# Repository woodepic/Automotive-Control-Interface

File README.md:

# Automotive-Control-Interface
A seamless user experience is critical for a well-engineered product. This project integrates a retrofitted button into the car's existing button backlighting system. This project includes designing the button, control interface, animations, and firmware from scratch. 

I wanted to add a button to my car for aftermarket heated windshield wipers, however I wanted to integrate it seamlessly into the vehicle. My car uses a single dimming control to dim every button and every screen in the car, so I wanted this existing dimmer to also dim my new button. This led me to tap into an existing button's backlight, use a voltage divider in my pcb to allow the arduino to read the signal, and use the arduino to measure the pulse width. Using a simple mapping function and the transisor-switched 12V power on my PCB, I can now match the new button's backlight to that of the car's. 

Image of the control PCB and the button:

I also wanted the button to look as though it belonged in the car. This led me to design and order a custom button. I designed a logo to indicate heated wipers, and ordered the button as a momentary, silver button, with a matching red backlight. Whenever the button is toggled on, a pulsing animation in the button's backlight begins. Whenever the button is off, the backlight matches that of other buttons, meaning in the daytime mode the backlight is off, and in the night-time mode the backlight is on. See the link at the bottom of this readme for a video demo. 

The arduino accepts various inputs: The momentary signal from the wiper button and the PWM signal from the car's existing button. The arduino calculates, and manages various outputs: power to the wiper button's backlight, a signal to a relay (toggles on/off the high-powered heated wipers), and an auxilary brightness output used to control the brightness of an aftermarket gauge.

As the cherry on top, all of the code including pulse animations are written to be non blocking, allowing other code to execute at the same time. I also implemented safety features such as built in fuses, a default to "wiper heat off" upon boot, and the power relay defaults to off in case of arduino failure.

Demo video of the project is found here: <https://youtu.be/XevvCuZYbWQ>

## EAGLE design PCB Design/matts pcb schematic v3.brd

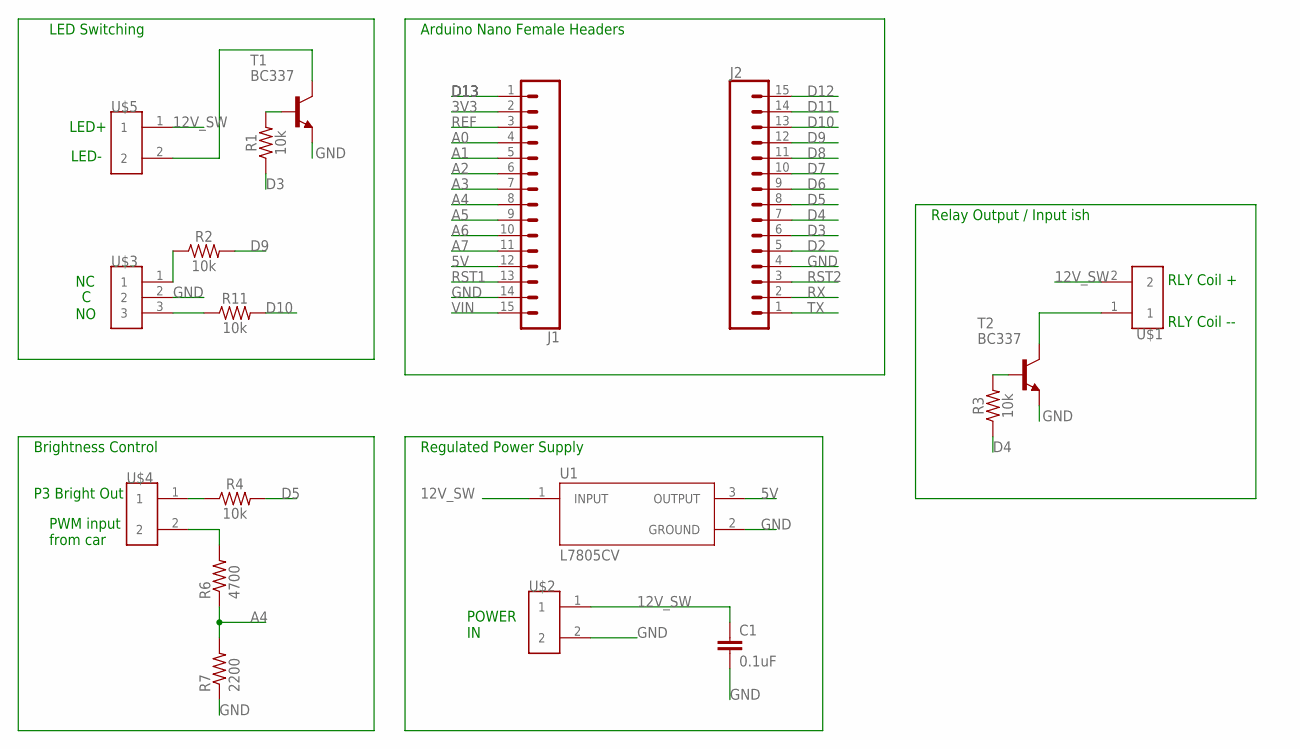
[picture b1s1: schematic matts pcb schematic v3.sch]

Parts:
C1: 0.1uF; CAP-PTH-SMALL-KIT
J1, J2: CONN_15; 1X15
R1, R2, R3, R4, R11: 10k; AXIAL-0.3
R6: 4700; 0207/10
R7: 2200; 0207/10
T1, T2: BC337; TO92
U1: L7805CV; TO255P1040X460X1968-3
U$1, U$2, U$4, U$5: 2PIN_0.2PITCH_SCREW_TERMINAL
U$3: 3PIN_0.2PITCH_SCREW_TERMINAL

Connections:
3V3: J1.2
5V: J1.12, U1.3 (OUTPUT)
12V_SW: C1.1, U1.1 (INPUT), U$1.2, U$2.1, U$5.1
A0: J1.4
A1: J1.5
A2: J1.6
A3: J1.7
A4: J1.8, R6.1, R7.2
A5: J1.9
A6: J1.10
A7: J1.11
D2: J2.5
D3: J2.6, R1.P$1 (1)
D4: J2.7, R3.P$1 (1)
D5: J2.8, R4.P$2 (2)
D6: J2.9
D7: J2.10
D8: J2.11
D9: J2.12, R2.P$2 (2)
D10: J2.13, R11.P$2 (2)
D11: J2.14
D12: J2.15
D13: J1.1
GND: C1.2, J1.14, J2.4, R7.1, T1.1 (E), T2.1 (E), U1.2 (GROUND), U$2.2, U$3.2
unnamed: R2.P$1 (1), U$3.1
unnamed: T2.3 (C), U$1.1
unnamed: R4.P$1 (1), U$4.1
unnamed: T1.3 (C), U$5.2
unnamed: R3.P$2 (2), T2.2 (B)
unnamed: R1.P$2 (2), T1.2 (B)
unnamed: R6.2, U$4.2
unnamed: R11.P$1 (1), U$3.3
REF: J1.3
RST1: J1.13
RST2: J2.3
RX: J2.2
TX: J2.1
VIN: J1.15

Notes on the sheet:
Arduino Nano Female Headers
LED+
LED-
Regulated Power Supply
LED Switching
Relay Output / Input ish
RLY Coil +
RLY Coil --
Brightness Control
P3 Bright Out
PWM input from car
POWER IN

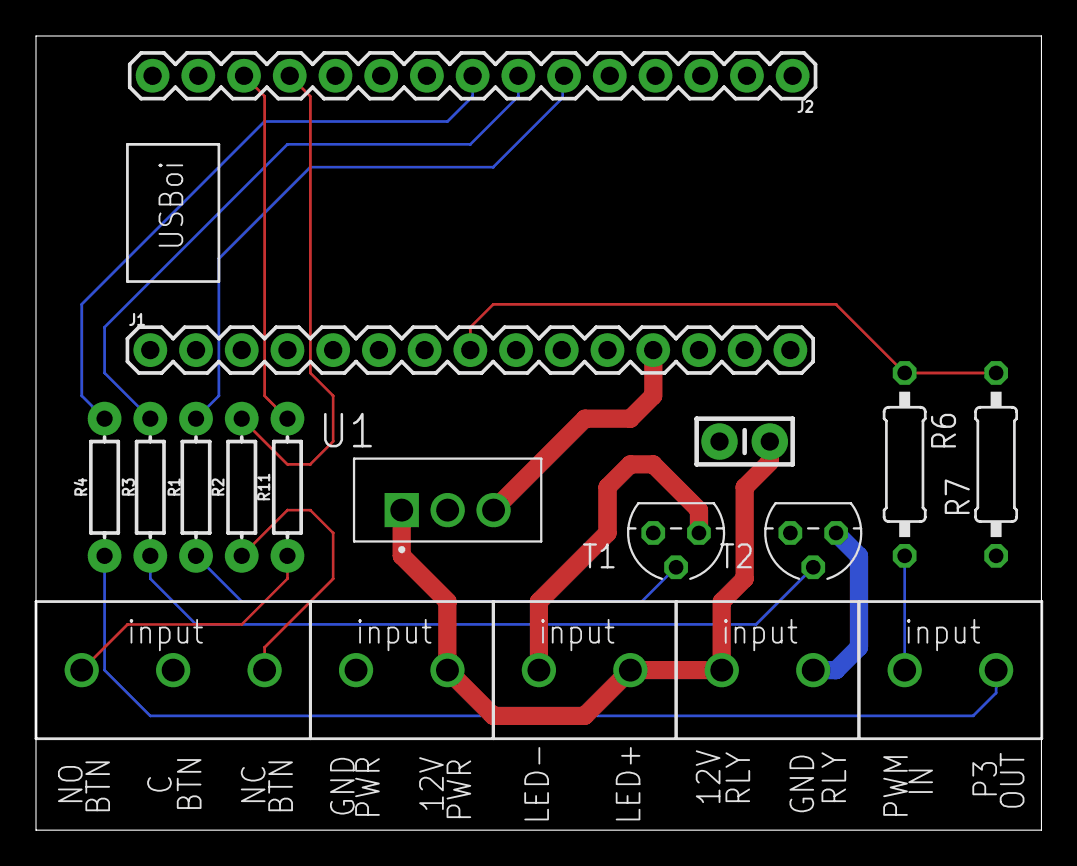
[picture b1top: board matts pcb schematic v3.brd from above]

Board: 2 copper layers, 55.9 x 44.1 mm, 18 parts (0 on the bottom side), 17 nets.

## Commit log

2022-01-21 Added images for readme
2022-01-21 Eagle project files
2022-01-21 Arduino Code

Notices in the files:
parts and their libraries:
SparkFun-Connectors: Licensing: Creative Commons ShareAlike 4.0 International - https://creativecommons.org/licenses/by-sa/4.0
